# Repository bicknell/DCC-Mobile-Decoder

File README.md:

# DCC-Mobile-Decoder
DCC Mobile Decoder Reference Implementation Hardware &amp; Software

## About

An open hardware and software implementation of a NMRA DCC compatable
Mobile Decoder using a PIC18 micro-processor.  The project aims to
make available a reference implementation of hardware and software to
facilitate software development, plus one or more decoder designs that
could be used in actual locomotives.

***This project is not yet complete and does not work in its current state.***

At this point the decoder can be connected to a DCC signal (ops mode) and 
correctly interprets speed, direction, functions f0-f12, ops mode CV programming,
and consisting.

Basic motor control has been implemented, but has not been tested with a real
motor.

Path to a working decoder:
  - [ ] Complete Hardware reference design - Breadboard-1. (Est 98% complete.)
  - [ ] Initial basic software for reference design. (Est 85% complete.)
    - CV's:
      - Obtain a manufacturer ID number?
        - Assign version numbers to decoders?
    - DCC Protocol:
      - Test/debug service mode programming, implemented but not tested.
      - Implement the "Factory Test" instruction?  What would it do?
      - Figure out what to send back for S-9.2.1 2.3.1.3 TTT=111 Decoder Acknowledgement Request
      - Pulse the motor for readback when in service mode.
      - Parse 11 bit DCC addresses?  Aren't they accessory decoder only?
      - Figure out if the Zimo East-West is 2 or 3 byte messages.
      - Handle S-9.2.1 2.3.6 CCC=110 Feature Expansion Instruction See TN-3-05
      - Handle S-9.2.3 Appendix B Service Mode Decoder LockA
    - Hardware Control:
      - Implement lighting effects.
      - Implement motor control.
        - Basic forward/reverse.
        - BackEMF adjustment.
        - Analog Mode?
    - Portability:
        - What needs to be done to make a common set of software that can be used
          across multiple decoder designs?
  - [ ] Initial real decoder design. (Proof of concept drafted.)
    - Draft of Wired-N-1A-6-1 has been produced.
    - Needs further mineaturization (e.g. more DFN components), and possible
      removal of gate resistors.
  - [ ] Documentation for above. (Est 60% complete.)

## Layout

* [docs/](docs/) documentation.
* [hardware/](hardware/) contains all materials related to hardware designs.
  This top level folder also includes a full index of the designs available.
  * [hardware/conventions/](hardware/conventions/) has a list of requirements
    for all hardware implementations so they can work with the common software.
  * [hardware/reference/](hardware/reference/) directory contains reference 
    implementations of decoder hardware.  These are designed to be easy to
    understand for teaching purposes, have a physical form factor to make
    them easy to use for prototyping with standard breadboards.  It my be
    possible to use them in locomotives, but that is not the primary purpose.
  * [hardware/decoders/](hardware/decoders/) directory contains specific
    decoders designed for specific applications.
* [software/](software/) contains all materials related to software code and build tools.
  * [software/common/](software/common/) common source code used across all
    decoder implementations.  ***FUTURE***
  * [software/reference/](software/reference/) source code for the reference
    implementation hardware.
  * [software/decoders/](software/decoders/) source code for specific decoders
    in [hardware/decoders/](hardware/decoders/).

## License

Licensed under the **Creative Commons Attribution-NonCommercial 4.0 
International Public License**, see the file [LICENSE](LICENSE) for
complete details.

Licenses for commerical use may be negotiated on a case by case basis.
Please contact project maintainers.  Any commercial terms negotiated
will include:

- A licensing term.
- An annual payments during the term that will be used to support
  the project.
- No royalties.
- A requirement to provide attribution in the instructions and on the
  packaging.

## Contributing

Please help us!

We would like to have a comprehensive library of hardware decoder designs
along with software implementations.  We want to enable everyone to build,
program, and modify their own DCC decoder.

Contributed material must be compatable with our license terms, project
goals, and project standards.

In particular we would like to encourage the following:

- New hardware designs for "drop in" decoders.
- Additional software features that make the software feature competitive
  with commercial decoders.
- Additional documentation to help others learn about DCC implementations.

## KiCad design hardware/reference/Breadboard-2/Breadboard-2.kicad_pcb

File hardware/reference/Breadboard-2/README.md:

# Breadboard-2

## About

The Breadboard-2 design was created to make development of software 
for a STM32 microcontroller as simple as possible.  The design goals were:

* Serve as a "reference design" for a decoder such that other designs
  could largely be done by omitting unnecessary elements and selecting
  new components.
* Fit a standard 400 or 830 tie point breadboard.
* Have a connector for a SW programmer.
* Operate over the full range of NMRA voltages to be scale independent.
* Have an easy to understand schmatic, suitable for teaching and that
  can be used as a basis for scale-specific decoders.
* Have an easy to understand PCB, suitable for teaching.
* Use low cost, over-specd, highly available, and easy to replace components.
* Include serial output capabilities for debugging.

## 3D Render

Actual size: 2" wide x 3" tall (not counting headers at top).

## Intended Use Case

It is expected that most users will connect the SW PROG and Serial headers
to use the board for software development activities.  Users who do not 
need external components (e.g. motors, or external function devices) can
simply solder power wires to the RL and RR inputs.  Users who want to
connect external devices would likely populate J1 and J2 and plug the
board into a standard 400 or 830 point breadboard.  The exposed connections
allow testing things like grain-of-wheat bulbs for lighting effects.

Although this decoder is not specifically intended to go in a locomotive
it could be installed in one.  This may be particularly useful when developing
motor control code.

## Schematic

View the [Breadboard-2.pdf](Breadboard-2.pdf) schematic without
having to open KiCad!

The document [CALCULATIONS.xlsx](CALCULATIONS.xlsx) contains a worksheet
for each schematic block with all of the relevant calculations.

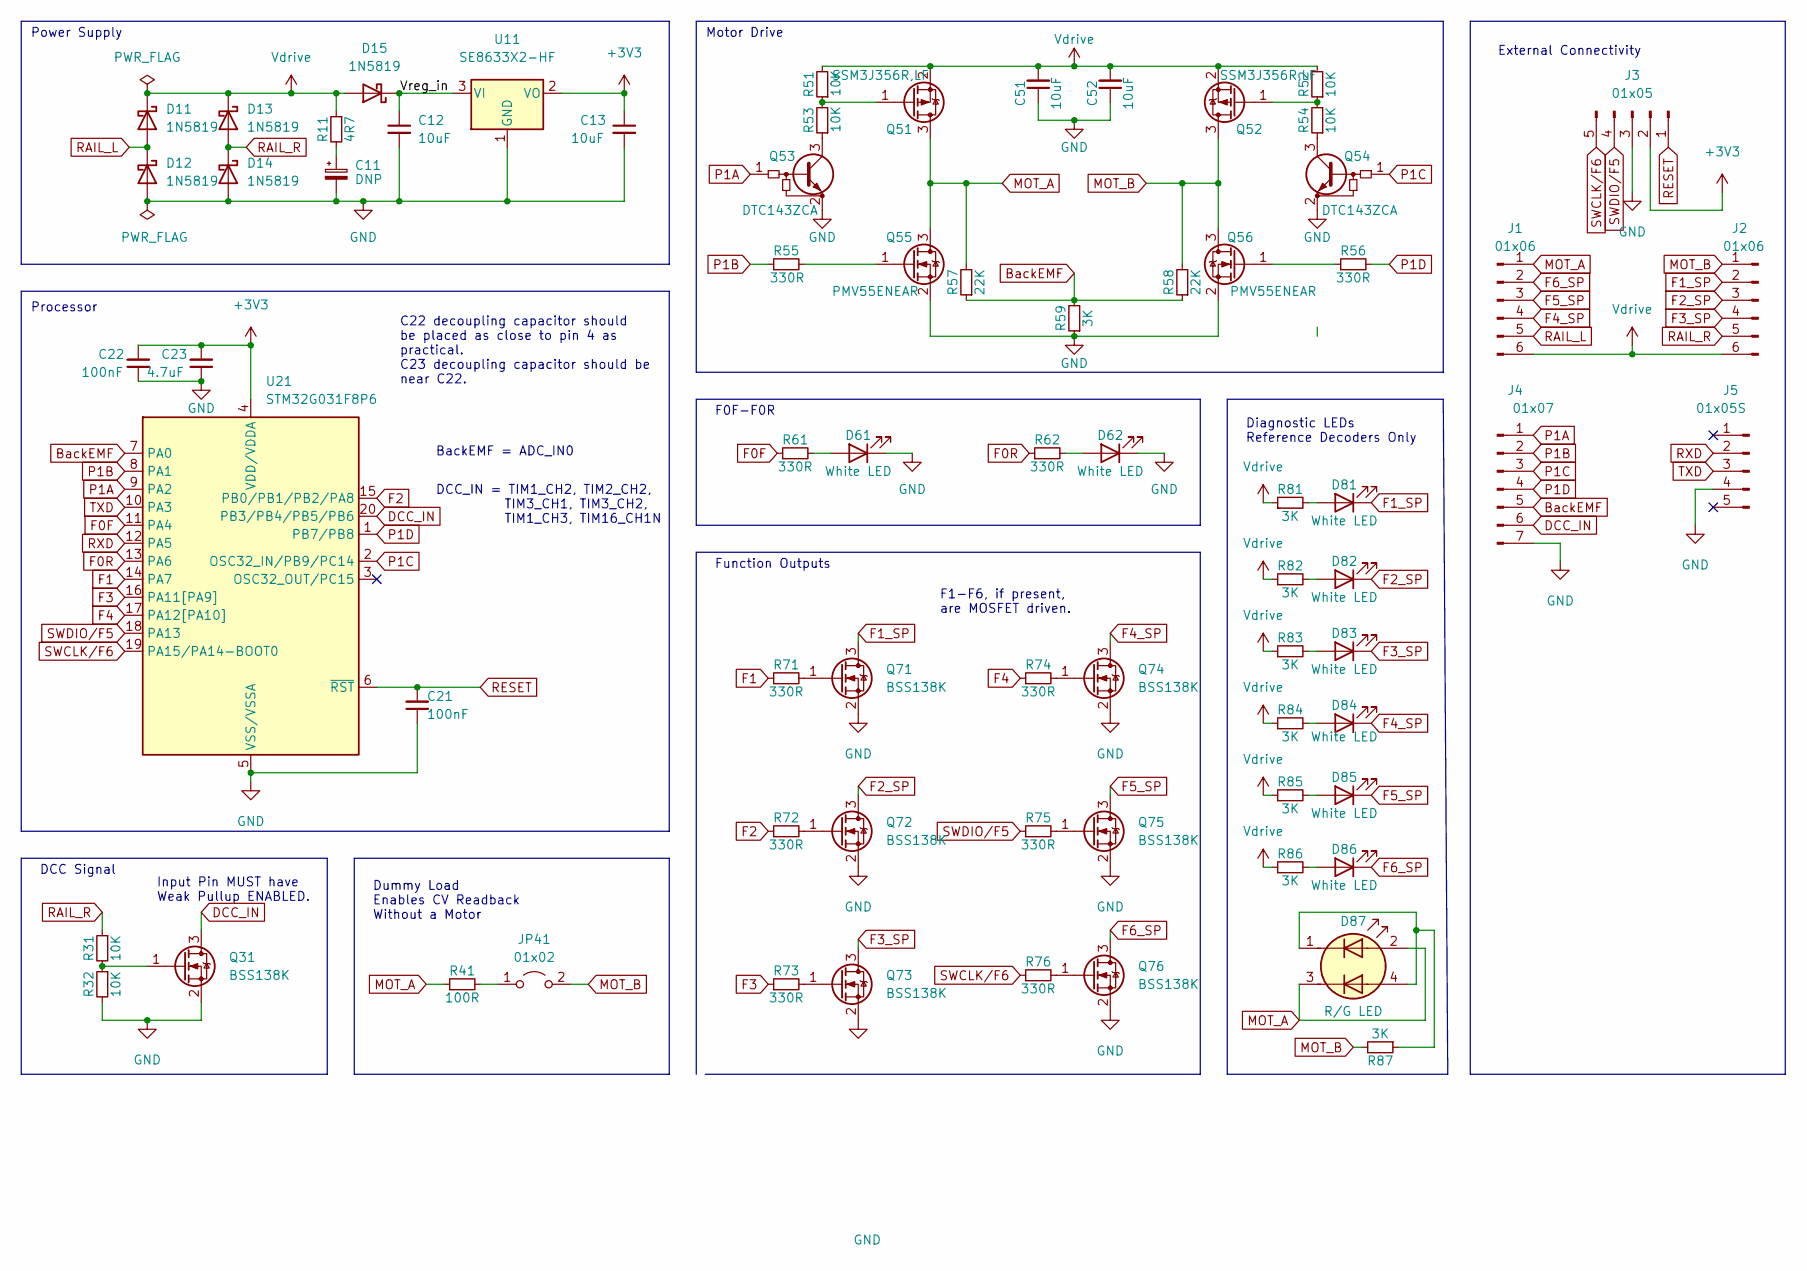
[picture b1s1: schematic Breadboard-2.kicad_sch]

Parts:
C11: DNP; CP_Radial_D10.0mm_P2.50mm_P5.00mm; MPN DNP; LCSC DNP
C12, C13, C51, C52: 10uF; C_0805_2012Metric; MPN Generic; LCSC C440198
C21, C22: 100nF; C_0805_2012Metric; MPN Generic; LCSC C49678
C23: 4.7uF; C_0805_2012Metric; MPN Generic; LCSC C49678
D11, D12, D13, D14, D15: 1N5819; D_SOD-323; MPN 1N5819WS; LCSC C191023
D61, D62, D81, D82, D83, D84, D85, D86: White LED; LED_0805_2012Metric; MPN KT-0805-W; LCSC C34499
D87: R/G LED; LED_RGB_1210; MPN XL-3227SURSYGC; LCSC C965843
J1, J2: 01x06; PinHeader_1x06_P2.54mm_Vertical; MPN DNP; LCSC DNP
J3: 01x05; PinHeader_1x05_P2.54mm_Horizontal; MPN DNP; LCSC DNP
J4: 01x07; PinHeader_1x07_P2.54mm_Vertical; MPN DNP; LCSC DNP
J5: 01x05S; PinSocket_1x05_P2.54mm_Horizontal; MPN DNP; LCSC DNP
JP41: 01x02; PinHeader_1x02_P2.54mm_Vertical; MPN DNP; LCSC DNP
Q31, Q71, Q72, Q73, Q74, Q75, Q76: BSS138K; SOT-23; MPN BSS138K; LCSC C5224263
Q51, Q52: SSM3J356R,LF; SOT-23; MPN SSM3J356R,LF; LCSC C146306
Q53, Q54: DTC143ZCA; SOT-23; MPN DTC143ZCA; LCSC C15236
Q55, Q56: PMV55ENEAR; SOT-23; MPN PMV55ENEAR; LCSC C294616
R11: 4R7; R_0805_2012Metric; MPN Generic; LCSC C17675
R31, R32, R51, R52, R53, R54: 10K; R_0805_2012Metric; MPN Generic; LCSC C17414
R41: 100R; R_2512_6332Metric; MPN RC2512JK-7W100RL; LCSC C876265
R55, R56, R61, R62, R71, R72, R73, R74, R75, R76: 330R; R_0805_2012Metric; MPN Generic; LCSC C17630
R57, R58: 22K; R_0805_2012Metric; MPN Generic; LCSC C17560
R59, R81, R82, R83, R84, R85, R86, R87: 3K; R_0805_2012Metric; MPN Generic; LCSC C17661
U11: SE8633X2-HF; SOT-23; MPN SE8633X2-HF; LCSC C496613
U21: STM32G031F8P6; TSSOP-20_4.4x6.5mm_P0.65mm; MPN STM32G031F8P6; LCSC C529334

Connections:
+3V3: C13.1, C22.2, C23.2, J3.2, U11.2 (VO), U21.4 (VDD/VDDA)
/Vreg_in: C12.1, D15.1 (K), U11.3 (VI)
BackEMF: J4.5, R57.1, R58.1, R59.2, U21.7 (PA0)
DCC_IN: J4.6, Q31.3 (D), U21.20 (PB3/PB4/PB5/PB6)
F0F: R61.1, U21.11 (PA4)
F0R: R62.1, U21.13 (PA6)
F1: R71.1, U21.14 (PA7)
F1_SP: D81.1 (K), J2.2, Q71.3 (D)
F2: R72.1, U21.15 (PB0/PB1/PB2/PA8)
F2_SP: D82.1 (K), J2.3, Q72.3 (D)
F3: R73.1, U21.16 (PA11[PA9])
F3_SP: D83.1 (K), J2.4, Q73.3 (D)
F4: R74.1, U21.17 (PA12[PA10])
F4_SP: D84.1 (K), J1.4, Q74.3 (D)
F5_SP: D85.1 (K), J1.3, Q75.3 (D)
F6_SP: D86.1 (K), J1.2, Q76.3 (D)
GND: C11.2, C12.2, C13.2, C21.1, C22.1, C23.1, C51.1, C52.1, D12.2 (A), D14.2 (A), D61.1 (K), D62.1 (K), J3.3, J4.7, J5.4, Q31.2 (S), Q53.2 (E), Q54.2 (E), Q55.2 (S), Q56.2 (S), Q71.2 (S), Q72.2 (S), Q73.2 (S), Q74.2 (S), Q75.2 (S), Q76.2 (S), R32.2, R59.1, U11.1 (GND), U21.5 (VSS/VSSA)
MOT_A: D87.2 (K1), D87.3 (A2), J1.1, Q51.3 (D), Q55.3 (D), R41.1, R57.2
MOT_B: J2.1, JP41.2 (B), Q52.3 (D), Q56.3 (D), R58.2, R87.2
unnamed: C11.1, R11.2
unnamed: D61.2 (A), R61.2
unnamed: D62.2 (A), R62.2
unnamed: D81.2 (A), R81.2
unnamed: D82.2 (A), R82.2
unnamed: D83.2 (A), R83.2
unnamed: D84.2 (A), R84.2
unnamed: D85.2 (A), R85.2
unnamed: D86.2 (A), R86.2
unnamed: D87.1 (A1), D87.4 (K2), R87.1
unnamed: JP41.1 (A), R41.2
unnamed: Q31.1 (G), R31.2, R32.1
unnamed: Q51.1 (G), R51.1, R53.2
unnamed: Q52.1 (G), R52.1, R54.2
unnamed: Q53.3 (C), R53.1
unnamed: Q54.3 (C), R54.1
unnamed: Q55.1 (G), R55.2
unnamed: Q56.1 (G), R56.1
unnamed: Q71.1 (G), R71.2
unnamed: Q72.1 (G), R72.2
unnamed: Q73.1 (G), R73.2
unnamed: Q74.1 (G), R74.2
unnamed: Q75.1 (G), R75.2
unnamed: Q76.1 (G), R76.2
P1A: J4.1, Q53.1 (B), U21.9 (PA2)
P1B: J4.2, R55.1, U21.8 (PA1)
P1C: J4.3, Q54.1 (B), U21.2 (OSC32_IN/PB9/PC14)
P1D: J4.4, R56.2, U21.1 (PB7/PB8)
RAIL_L: D11.2 (A), D12.1 (K), J1.5
RAIL_R: D13.2 (A), D14.1 (K), J2.5, R31.1
RESET: C21.2, J3.1, U21.6 (~RST)
RXD: J5.2, U21.12 (PA5)
SWCLK/F6: J3.5, R76.1, U21.19 (PA15/PA14-BOOT0)
SWDIO/F5: J3.4, R75.1, U21.18 (PA13)
TXD: J5.3, U21.10 (PA3)
Vdrive: C51.2, C52.2, D11.1 (K), D13.1 (K), D15.2 (A), J1.6, J2.6, Q51.2 (S), Q52.2 (S), R11.1, R51.2, R52.2, R81.1, R82.1, R83.1, R84.1, R85.1, R86.1

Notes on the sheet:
DCC Signal
F0F-F0R
Input Pin MUST have Weak Pullup ENABLED.
BackEMF = ADC_IN0
Function Outputs
Power Supply
External Connectivity
F1-F6, if present, are MOSFET driven.
Diagnostic LEDs Reference Decoders Only
Motor Drive
DCC_IN = TIM1_CH2, TIM2_CH2, TIM3_CH1, TIM3_CH2, TIM1_CH3, TIM16_CH1N
C22 decoupling capacitor should be placed as close to pin 4 as practical. C23 decoupling capacitor should be near C22.
Processor
Dummy Load Enables CV Readback Without a Motor

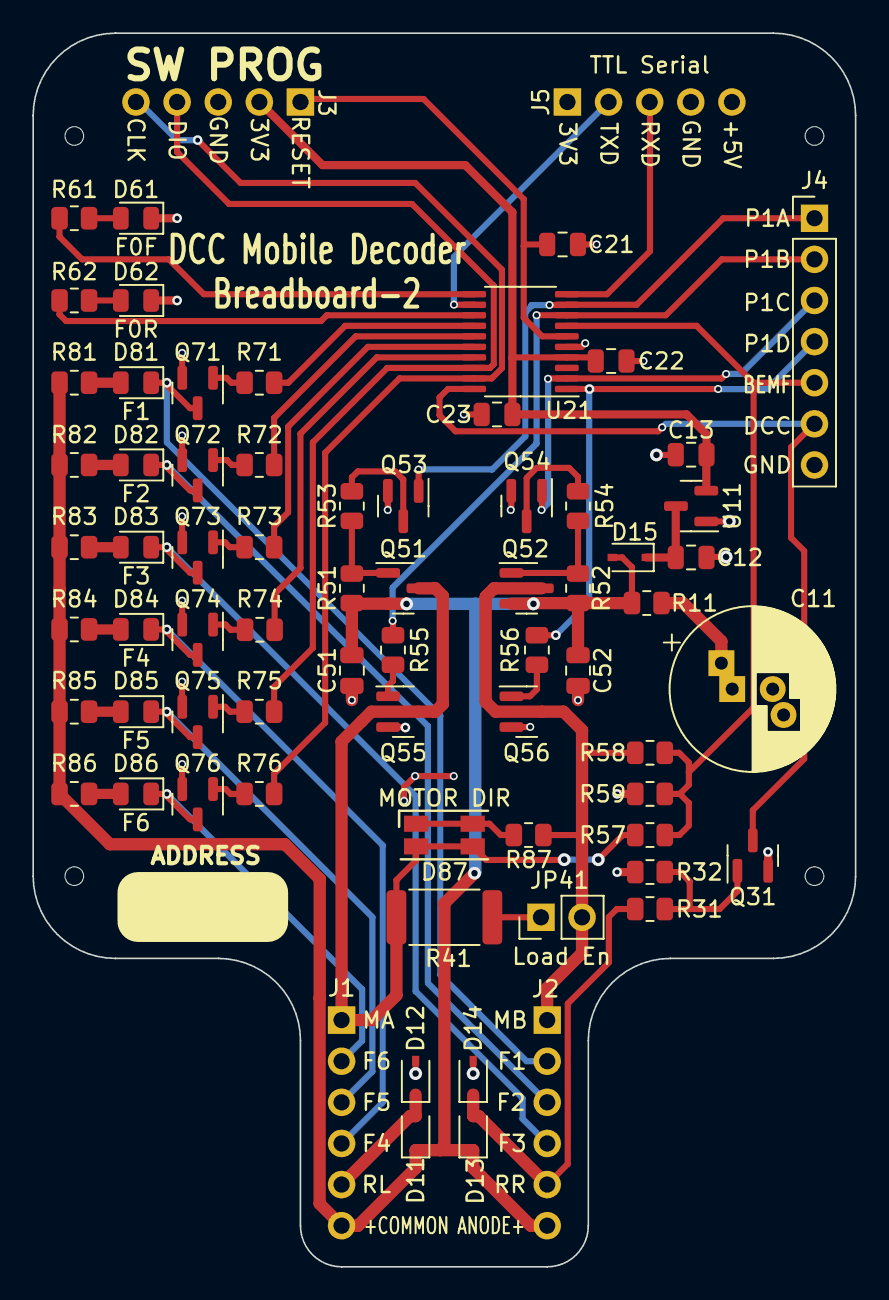
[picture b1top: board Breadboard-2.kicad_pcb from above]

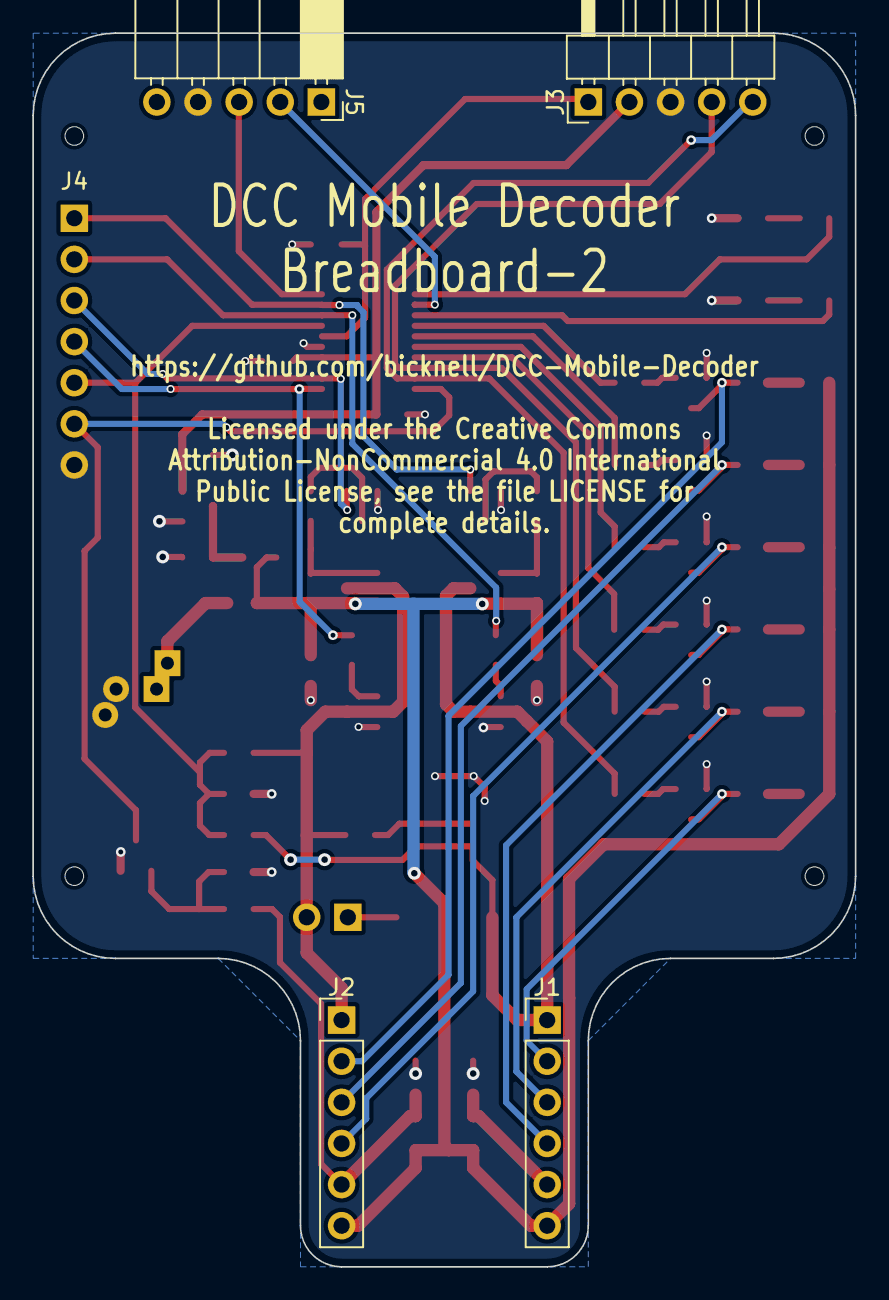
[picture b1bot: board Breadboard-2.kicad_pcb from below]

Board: 2 copper layers, 50.8 x 76.2 mm, 71 parts (4 on the bottom side), 55 nets.

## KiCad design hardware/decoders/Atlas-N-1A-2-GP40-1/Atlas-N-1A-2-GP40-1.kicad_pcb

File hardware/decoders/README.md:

# Index of Decoders

* [Wired-N-1A-8-1](Wired-N-1A-8-1/) Solder Pads, N scale, 1A, 8 function, 9mm x 25mm

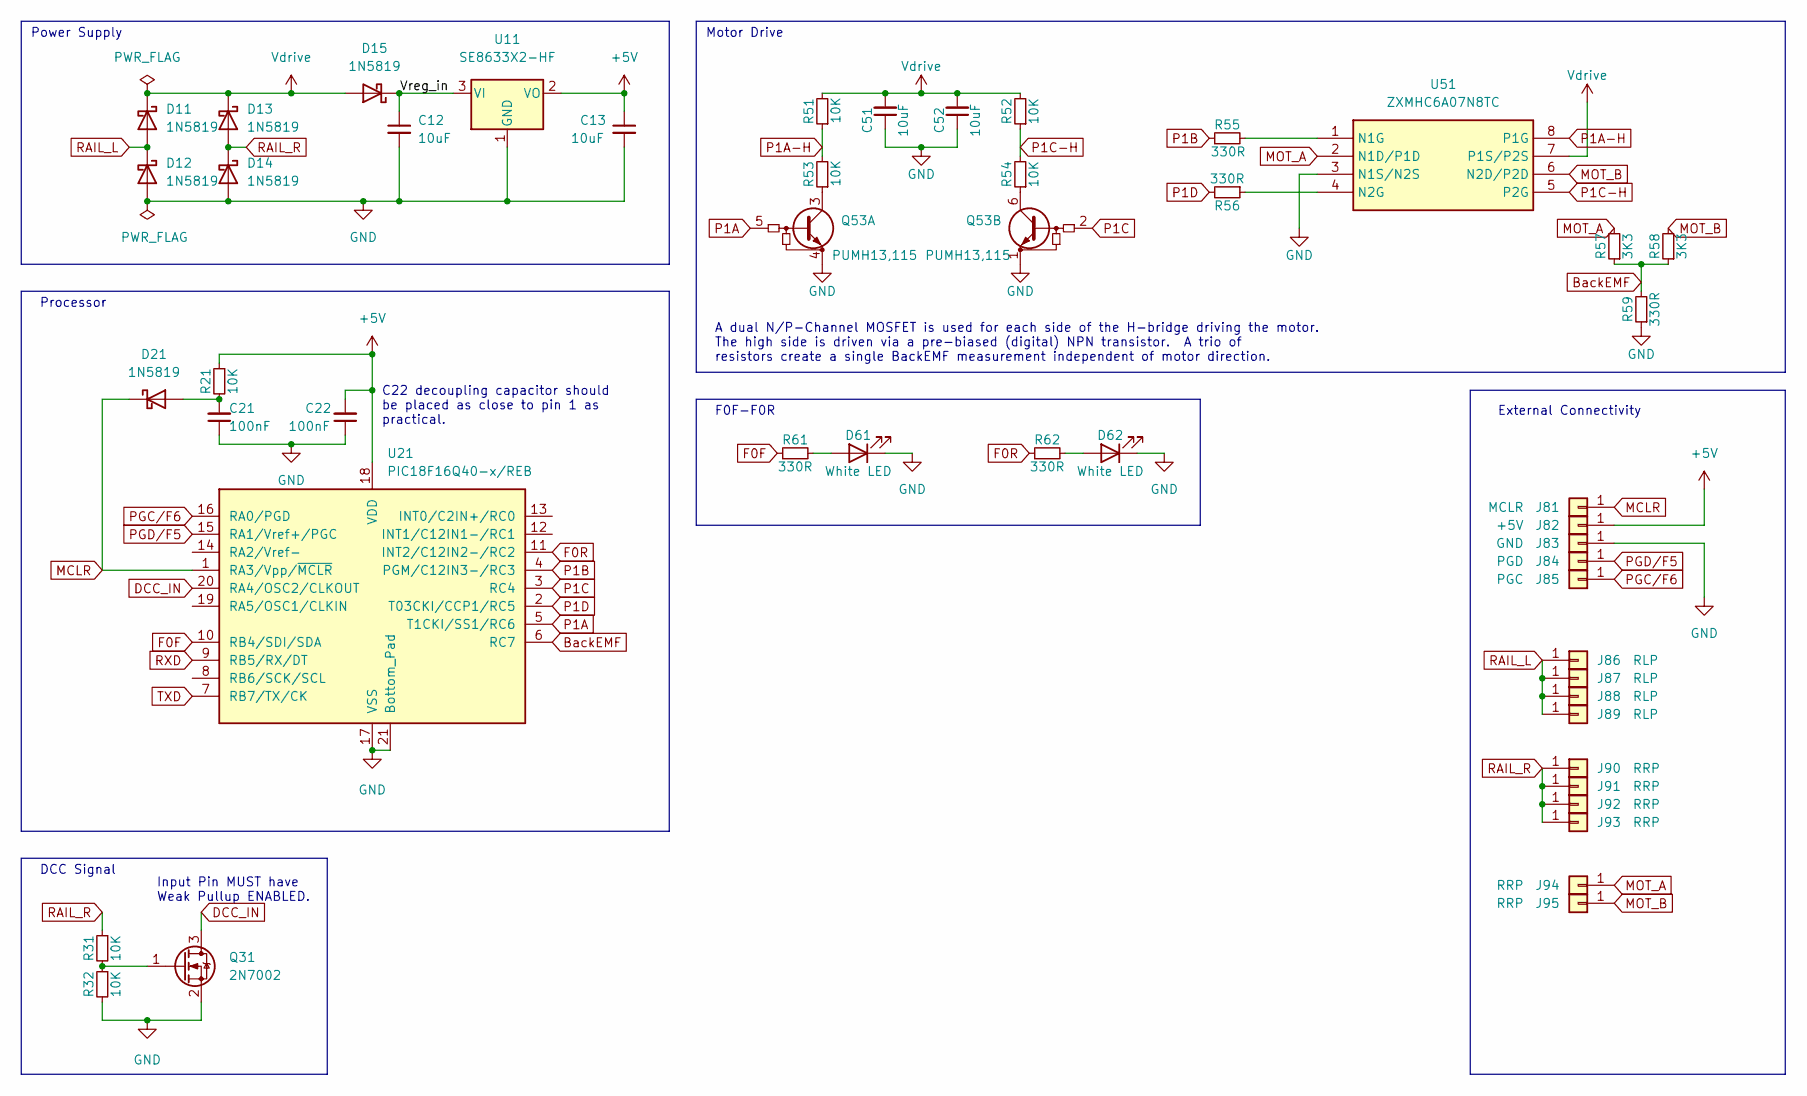
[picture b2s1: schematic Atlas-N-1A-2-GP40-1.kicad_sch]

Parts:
C12, C13, C51, C52: 10uF; C_0805_2012Metric; MPN GRM21BR61H106KE43L; LCSC C440198
C21, C22: 100nF; C_0402_1005Metric; MPN CL05B104KO5NNNC; LCSC C1525
D11, D12, D13, D14, D15, D21: 1N5819; D_SOD-323; MPN 1N5819WS; LCSC C191023
D61, D62: White LED; LED_0402_1005Metric; MPN KT-0805-W; LCSC C34499
J81: MCLR; EP-1.5mmx3mm; MPN DNP; LCSC DNP
J82: +5V; EP-1.5mmx3mm; MPN DNP; LCSC DNP
J83: GND; EP-1.5mmx3mm; MPN DNP; LCSC DNP
J84: PGD; EP-1.5mmx3mm; MPN DNP; LCSC DNP
J85: PGC; EP-1.5mmx3mm; MPN DNP; LCSC DNP
J86, J87, J88, J89: RLP; EP-1.5mmx3mm; MPN DNP; LCSC DNP
J90, J91, J92, J93: RRP; EP-1.5mmx3mm; MPN DNP; LCSC DNP
J94: RRP; EP-2.5mmx3mm; MPN DNP; LCSC DNP
J95: RRP; EP-2.5mmx5mm; MPN DNP; LCSC DNP
Q31: 2N7002; SOT-23; MPN 2N7002; LCSC C8545
Q53: PUMH13,115; SOT-363_SC-70-6; MPN PUMH13,115; LCSC C426875
R21, R31, R32, R51, R52, R53, R54: 10K; R_0402_1005Metric; MPN 0402WGF1502TCE; LCSC C25744
R55, R56, R59, R61, R62: 330R; R_0402_1005Metric; MPN 0402WGF3300TCE; LCSC C25104
R57, R58: 3K3; R_0402_1005Metric; MPN 0402WGF3301TCE; LCSC C25890
U11: SE8633X2-HF; SOT-23; MPN SE8633X2-HF; LCSC C496613
U21: PIC18F16Q40-x/REB; VQFN-20-1EP_3x3mm_P0.4mm_EP1.7x1.7mm; MPN PIC18F16Q40-I/REB; LCSC C3216898
U51: ZXMHC6A07N8TC; SOIC-8_3.9x4.9mm_P1.27mm; MPN ZXMHC6A07N8TC; LCSC C460274

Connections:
+5V: C13.1, C22.2, J82.1, R21.1, U11.2 (VO), U21.18 (VDD)
/Vreg_in: C12.1, D15.1 (K), U11.3 (VI)
BackEMF: R57.1, R58.1, R59.2, U21.6 (RC7)
DCC_IN: Q31.3 (D), U21.20 (RA4/OSC2/CLKOUT)
F0F: R61.1, U21.10 (RB4/SDI/SDA)
F0R: R62.1, U21.11 (INT2/C12IN2-/RC2)
GND: C12.2, C13.2, C21.1, C22.1, C51.1, C52.1, D12.2 (A), D14.2 (A), D61.1 (K), D62.1 (K), J83.1, Q31.2 (S), Q53.1 (E2), Q53.4 (E1), R32.2, R59.1, U11.1 (GND), U21.17 (VSS), U21.21 (Bottom_Pad), U51.3 (N1S/N2S)
MCLR: D21.1 (K), J81.1, U21.1 (RA3/Vpp/~MCLR)
MOT_A: J94.1, R57.2, U51.2 (N1D/P1D)
MOT_B: J95.1, R58.2, U51.6 (N2D/P2D)
unnamed: C21.2, D21.2 (A), R21.2
unnamed: D61.2 (A), R61.2
unnamed: D62.2 (A), R62.2
unnamed: Q31.1 (G), R31.2, R32.1
unnamed: Q53.3 (C1), R53.1
unnamed: Q53.6 (C2), R54.1
unnamed: R55.2, U51.1 (N1G)
unnamed: R56.1, U51.4 (N2G)
P1A: Q53.5 (B1), U21.5 (T1CKI/SS1/RC6)
P1A-H: R51.1, R53.2, U51.8 (P1G)
P1B: R55.1, U21.4 (PGM/C12IN3-/RC3)
P1C: Q53.2 (B2), U21.3 (RC4)
P1C-H: R52.1, R54.2, U51.5 (P2G)
P1D: R56.2, U21.2 (T03CKI/CCP1/RC5)
PGC/F6: J85.1, U21.16 (RA0/PGD)
PGD/F5: J84.1, U21.15 (RA1/Vref+/PGC)
RAIL_L: D11.2 (A), D12.1 (K), J86.1, J87.1, J88.1, J89.1
RAIL_R: D13.2 (A), D14.1 (K), J90.1, J91.1, J92.1, J93.1, R31.1
RXD: U21.9 (RB5/RX/DT)
TXD: U21.7 (RB7/TX/CK)
Vdrive: C51.2, C52.2, D11.1 (K), D13.1 (K), D15.2 (A), R51.2, R52.2, U51.7 (P1S/P2S)

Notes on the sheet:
DCC Signal
F0F-F0R
Input Pin MUST have Weak Pullup ENABLED.
Power Supply
External Connectivity
Motor Drive
C22 decoupling capacitor should be placed as close to pin 1 as practical.
A dual N/P-Channel MOSFET is used for each side of the H-bridge driving the motor. The high side is driven via a pre-biased (digital) NPN transistor. A trio of resistors create a single BackEMF measurement independent of motor direction.
Processor

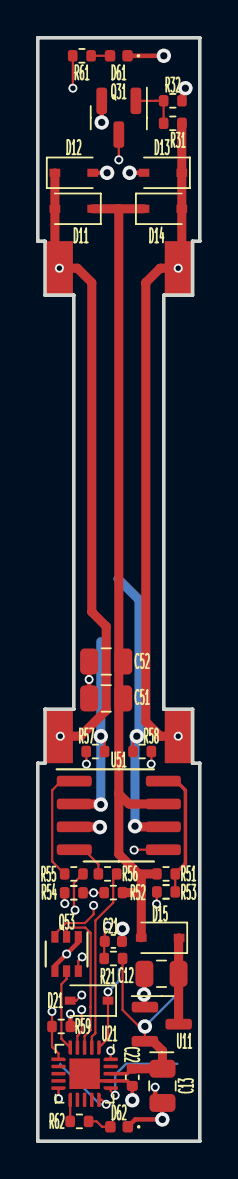
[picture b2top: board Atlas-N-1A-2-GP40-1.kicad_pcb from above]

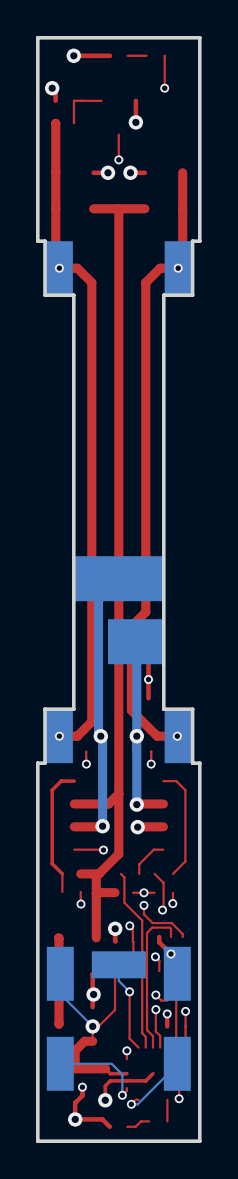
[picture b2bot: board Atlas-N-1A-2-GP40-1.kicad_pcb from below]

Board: 4 copper layers, 9.0 x 61.3 mm, 48 parts (11 on the bottom side), 29 nets.

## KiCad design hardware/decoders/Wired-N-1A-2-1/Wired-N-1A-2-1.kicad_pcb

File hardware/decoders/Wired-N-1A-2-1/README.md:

# Wired-N-1A-2-1

## About

The Wired-N-1A-2-1 design is a basic 1A N-Scale decoder based off the 
Breadboard-1 reference design.

* 1A Capacity
* 2 Functions (FOF, FOR)
* ICSP programming exposed via pads.
* Components on top side only enabling cheap fabrication.

## 3D Render

Actual size 9mm x 18mm:

## Intended Use Case

Used for any hard wired N/Z scale application, from locomotives
that do not support drop in decoders, to passenger car and caboose
lighting operations.

## Schematic

View the schematic: [Wired-N-1A-2-1.pdf](Wired-N-1A-2-1.pdf)

Supporting [CALCULATIONS.md](CALCULATIONS.md) discussions how component values were determined.

## Schematic Walkthrough

### Power Supply

Power from the two rails is fed into a bridge rectifier made up of
four discrete diodes D11-D14.  As DCC is a square wave, the output
is nearly but not quite continuous DC power with low ripple.  That
power is split off to drive the motor and functions directly, labeled
as Vdrive.  A linear regulator U11 is used to generate +5v for the
micro-processor, and has two support capacitors.

The project requirements for this design are to operate from 6v to 30v
of input.

### Micro-controller

A PIC18F06Q40 processor is used in this design due to it's avaialbility
in a 3mm x 3mm VQFN-20 package.  PIC processors require minimal
support components.  C21 is a local bypass capacitor that is placed
closed to the power pins.  C23 and R11 form a hold up circuit for
MCLR which must be kept high during normal operation.  If MCLR
drops, the chip will reset.

Particular notes on this part:

- This design does not use a Vref pin.

### H-Bridge

The H-Bridge controls the current to the motor.  It is driven by a PWM signal generated
by the micro-controller.  The software generates 4 PWM signals, P1A-P1D, which are used
to control speed and direction.

The H-bridge is simply 4 high power MOSFETs arranged in an H
configuration.  This design uses two discrete dual MOSFET chips
each with 1 PNP and 1NPN MOSFET, which is a common arrangement.
Resistors are placed on the gate inputs to prevent inrush from
damaging the micro-controller.

External diodes are omitted on this design to save space, the body
diode of the MOSFET must do the job.

In order to calculate BackEMF, a 100nf capacitor C31 is added to
reduce signal noise.  The resistors R35 and R36 then reduce the
voltage to an appropriate level for the analog input of the
micro-controller.  By monitoring this voltage the micro-controller
can calculate the load.

### Functions

This design supports functions F0F, F0R, F1-F6.

Functions F0F, F0R, and F1-F6 are designed to be connected to
external device in a "common anode" configuration.

Vdrive power is provided as a common anode source at both ends of
the board.  The MOSFET connects to ground when turned on by the
micro-processor.  A resistor is provided on the gate of each MOSFET
to manage inrush current.

### External Connectivity

MA & MB are the two motor connection solder pads.

RL & RR are the left and right rail solder pads.

F0F, F0R, & F0-F6 are the function solder pads.

CA are the Common Anode solder pads.

MCLR, +5, GND, PGD, PGD make up the ISCP connection points.

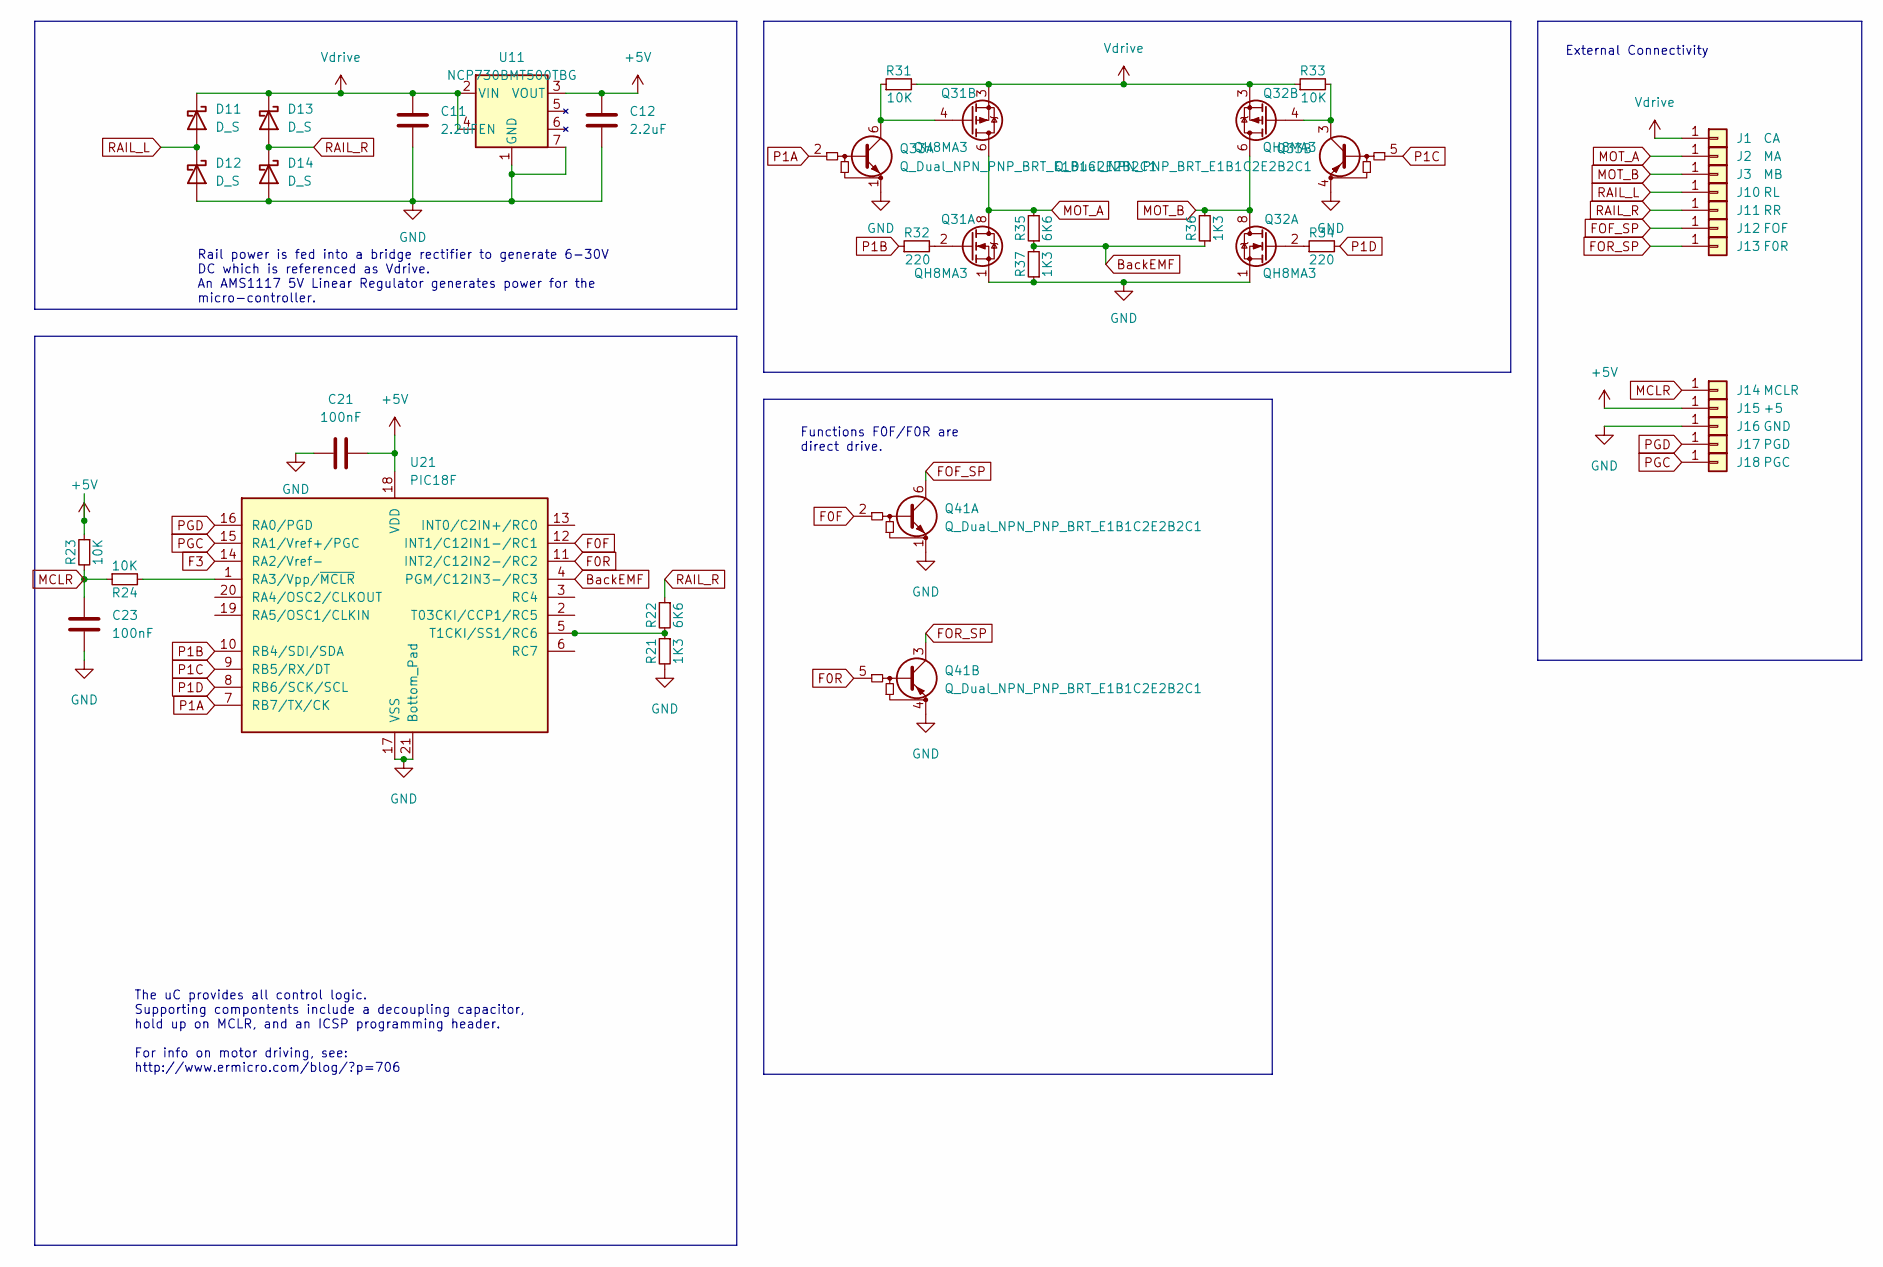
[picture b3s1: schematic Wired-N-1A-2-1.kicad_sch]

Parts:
C11, C12: 2.2uF; C_0402_1005Metric; MPN1 GRM155R6YA225KE11D
C21, C23: 100nF; C_0201_0603Metric; MPN1 GRM033R61E104KE14D
D11, D12, D13, D14: D_S; D_SOD-523; MPN1 MSK4010
J1: CA; SolderWirePad_1x01_SMD_1x2mm; MPN1 DNP
J2: MA; SolderWirePad_1x01_SMD_1x2mm; MPN1 DNP
J3: MB; SolderWirePad_1x01_SMD_1x2mm; MPN1 DNP
J10: RL; SolderWirePad_1x01_SMD_1x2mm; MPN1 DNP
J11: RR; SolderWirePad_1x01_SMD_1x2mm; MPN1 DNP
J12: FOF; SolderWirePad_1x01_SMD_1x2mm; MPN1 DNP
J13: F0R; SolderWirePad_1x01_SMD_1x2mm; MPN1 DNP
J14: MCLR; SolderWirePad_1x01_SMD_1x2mm; MPN1 DNP
J15: +5; SolderWirePad_1x01_SMD_1x2mm; MPN1 DNP
J16: GND; SolderWirePad_1x01_SMD_1x2mm; MPN1 DNP
J17: PGD; SolderWirePad_1x01_SMD_1x2mm; MPN1 DNP
J18: PGC; SolderWirePad_1x01_SMD_1x2mm; MPN1 DNP
Q31, Q32: QH8MA3; TSMT8; MPN1 QH8MA3 QH8MA3
Q33, Q41: Q_Dual_NPN_PNP_BRT_E1B1C2E2B2C1; SOT-666
R21, R36, R37: 1K3; R_0201_0603Metric; MPN1 0201WMF1331TEE
R22, R35: 6K6; R_0201_0603Metric; MPN1 0201WMF665KTEE
R23, R24: 10K; R_0201_0603Metric; MPN1 0201WMF1002TEE
R31, R33: 10K; R_0201_0603Metric; MPN1 0201WMF2200TEE
R32, R34: 220; R_0201_0603Metric; MPN1 0201WMF2200TEE
U11: NCP730BMT500TBG; DFN-6-1EP_2x2mm_P0.65mm_EP1x1.6mm; MPN1 NCP730BMT500TBG
U21: PIC18F; VQFN-20-1EP_3x3mm_P0.4mm_EP1.7x1.7mm; MPN1 PIC18F06Q40

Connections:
+5V: C12.1, C21.2, J15.1, R23.1, U11.3 (VOUT), U21.18 (VDD)
BackEMF: R35.1, R36.1, R37.2, U21.4 (PGM/C12IN3-/RC3)
F0F: Q41.2 (B1), U21.12 (INT1/C12IN1-/RC1)
F0R: Q41.5 (B1), U21.11 (INT2/C12IN2-/RC2)
F3: U21.14 (RA2/Vref-)
FOF_SP: J12.1, Q41.6 (C1)
FOR_SP: J13.1, Q41.3 (C1)
GND: C11.2, C12.2, C21.1, C23.1, D12.2 (A), D14.2 (A), J16.1, Q31.1 (S), Q32.1 (S), Q33.1 (E1), Q33.4 (E1), Q41.1 (E1), Q41.4 (E1), R21.2, R37.1, U11.1 (GND), U11.7, U21.17 (VSS), U21.21 (Bottom_Pad)
MCLR: C23.2, J14.1, R23.2, R24.1
MOT_A: J2.1, Q31.5 (D), Q31.6 (D), Q31.7 (D), Q31.8 (D), R35.2
MOT_B: J3.1, Q32.5 (D), Q32.6 (D), Q32.7 (D), Q32.8 (D), R36.2
unnamed: Q31.2 (G), R32.2
unnamed: Q31.4 (G), Q33.6 (C1), R31.1
unnamed: Q32.2 (G), R34.1
unnamed: Q32.4 (G), Q33.3 (C1), R33.2
unnamed: R21.1, R22.2, U21.5 (T1CKI/SS1/RC6)
unnamed: R24.2, U21.1 (RA3/Vpp/~MCLR)
P1A: Q33.2 (B1), U21.7 (RB7/TX/CK)
P1B: R32.1, U21.10 (RB4/SDI/SDA)
P1C: Q33.5 (B1), U21.9 (RB5/RX/DT)
P1D: R34.2, U21.8 (RB6/SCK/SCL)
PGC: J18.1, U21.15 (RA1/Vref+/PGC)
PGD: J17.1, U21.16 (RA0/PGD)
RAIL_L: D11.2 (A), D12.1 (K), J10.1
RAIL_R: D13.2 (A), D14.1 (K), J11.1, R22.1
Vdrive: C11.1, D11.1 (K), D13.1 (K), J1.1, Q31.3 (1), Q32.3 (1), R31.2, R33.1, U11.2 (VIN), U11.4 (EN)

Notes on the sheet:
External Connectivity
The uC provides all control logic. Supporting compontents include a decoupling capacitor, hold up on MCLR, and an ICSP programming header. For info on motor driving, see: http://www.ermicro.com/blog/?p=706
Functions F0F/F0R are direct drive.
Rail power is fed into a bridge rectifier to generate 6-30V DC which is referenced as Vdrive. An AMS1117 5V Linear Regulator generates power for the micro-controller.

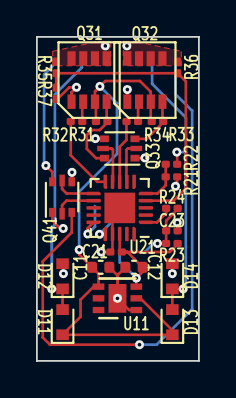
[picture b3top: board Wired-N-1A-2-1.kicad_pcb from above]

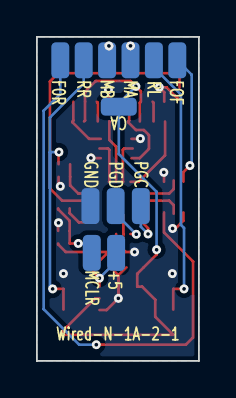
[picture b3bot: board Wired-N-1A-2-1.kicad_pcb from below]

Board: 2 copper layers, 9.0 x 18.0 mm, 37 parts (12 on the bottom side), 25 nets.

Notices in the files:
software/reference/Breadboard-1.X/mcc_generated_files/pin_manager.h:
(c) 2018 Microchip Technology Inc. and its subsidiaries.
hardware/reference/Breadboard-2/Breadboard-2.kicad_pcb:
Public License, see the file LICENSE for
